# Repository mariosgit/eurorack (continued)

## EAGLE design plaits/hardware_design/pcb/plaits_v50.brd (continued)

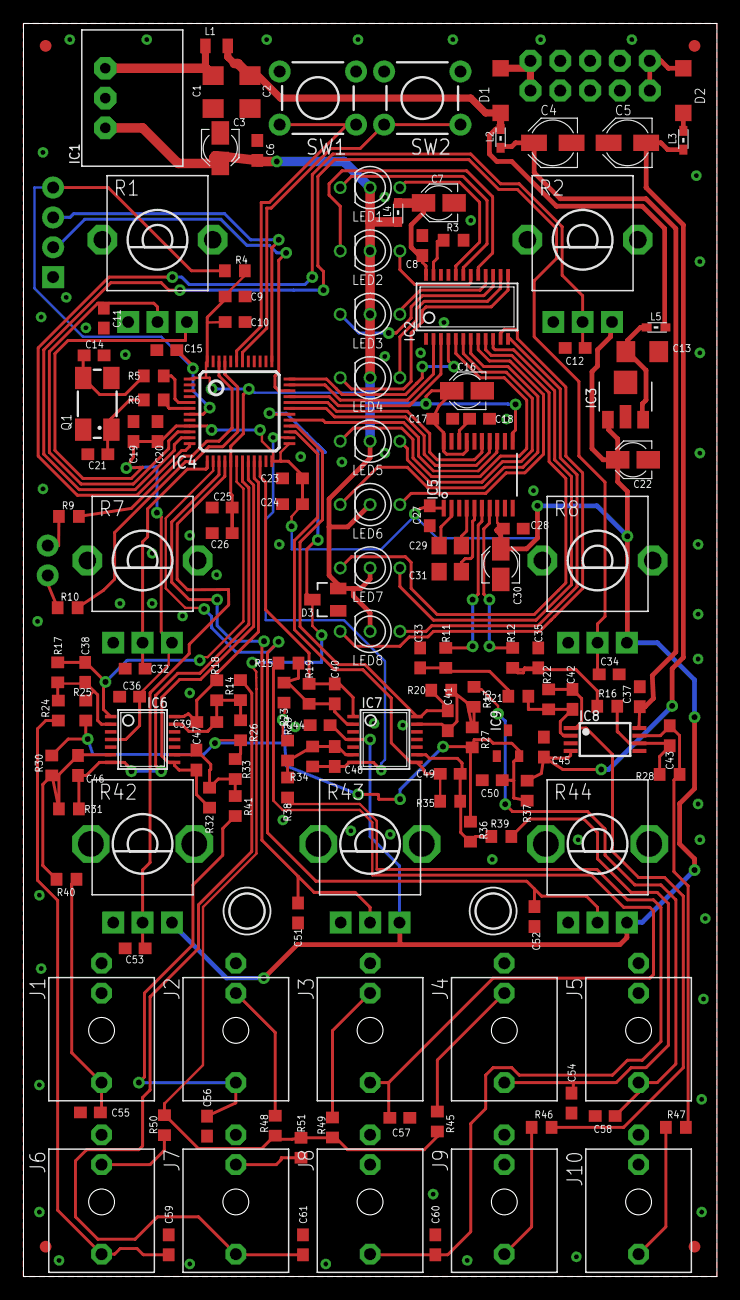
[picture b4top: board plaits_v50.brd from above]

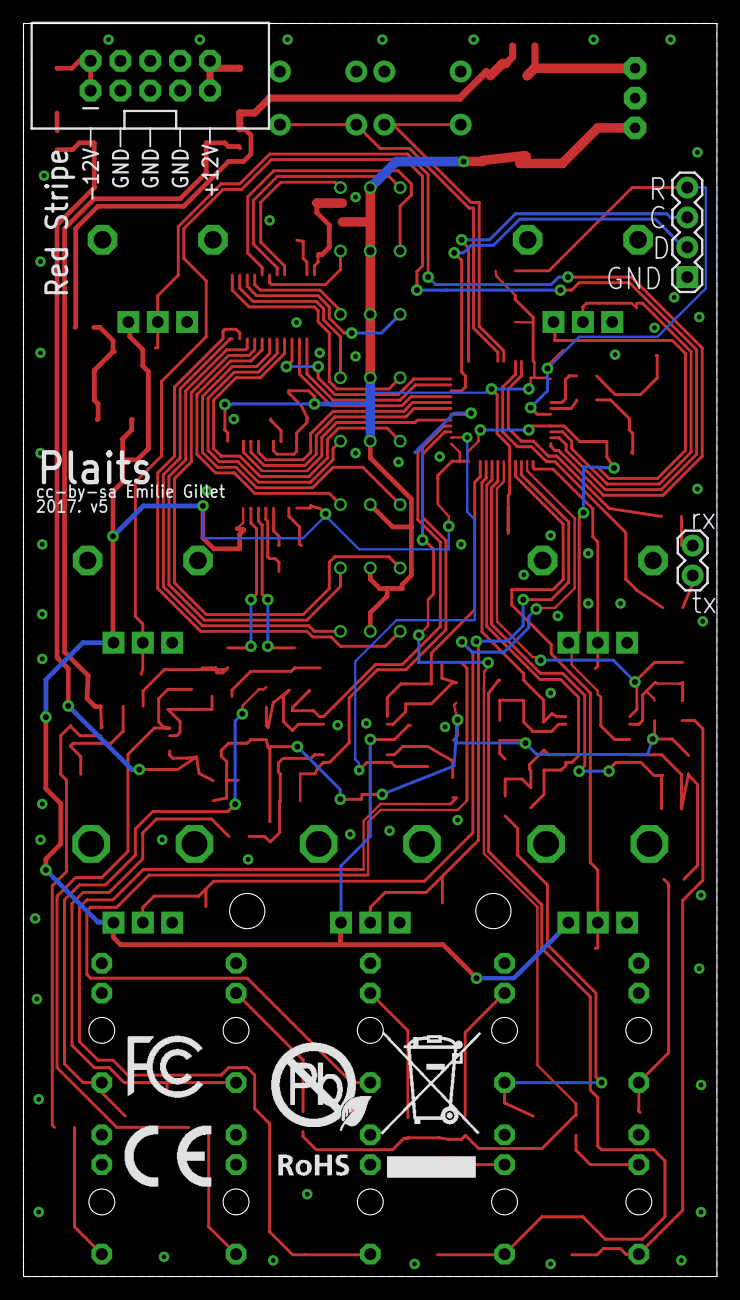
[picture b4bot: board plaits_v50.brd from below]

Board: 2 copper layers, 59.0 x 106.7 mm, 162 parts (6 on the bottom side), 100 nets.

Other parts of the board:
U$1: FCC_MEDIUM
U$2: ROHS_BIG
U$3: CE_MEDIUM

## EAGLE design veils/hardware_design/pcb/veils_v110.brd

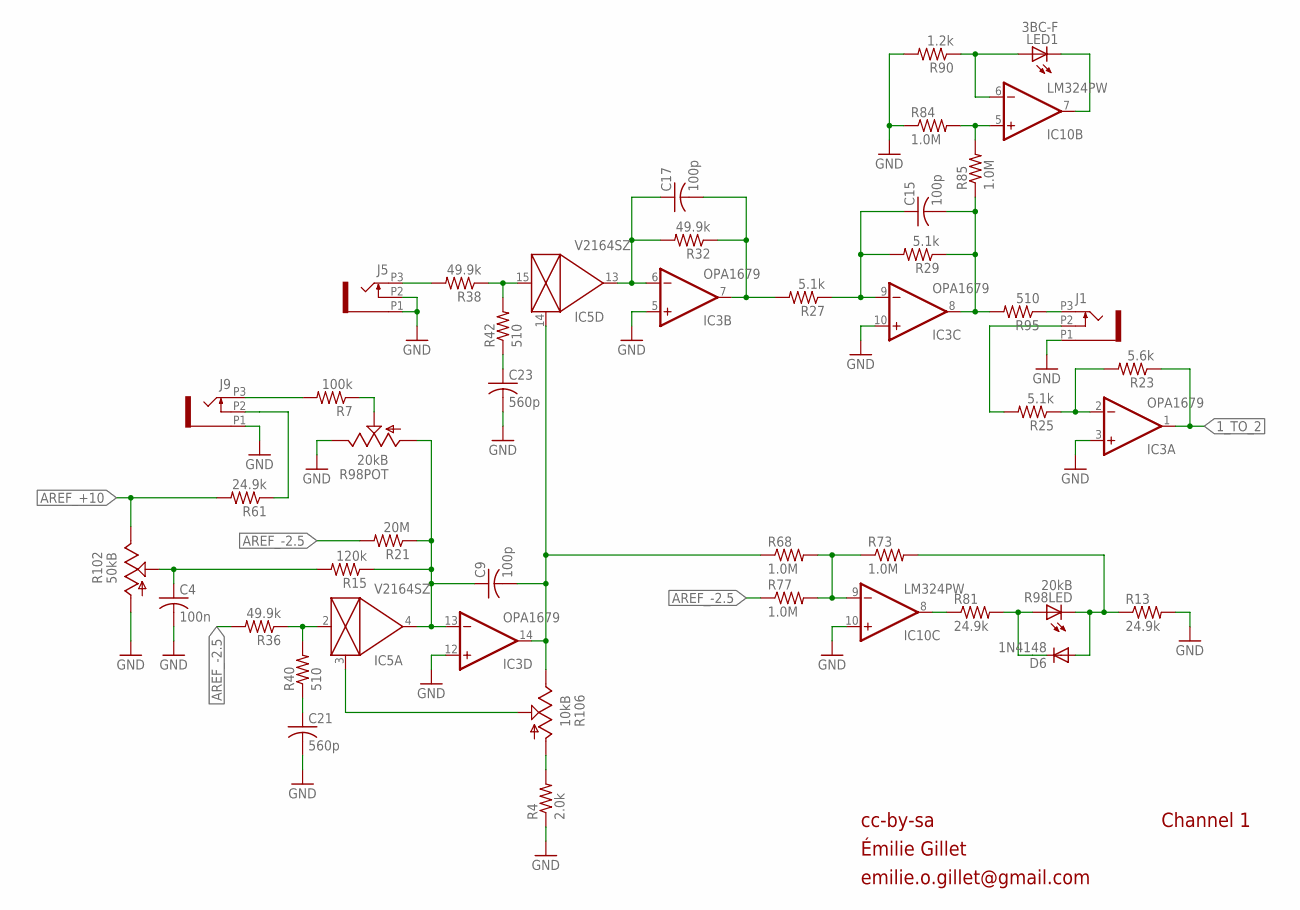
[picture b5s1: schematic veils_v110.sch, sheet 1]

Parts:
C4: 100n; C0402
C9, C15, C17: 100p; C0402
C21, C23: 560p; C0402
D6: 1N4148; SOD523
IC3: OPA1679; TSSOP14_065
IC5: V2164SZ; SOIC16N
IC10: LM324PW; TSSOP14_065
J1, J5, J9: PJ301_THONKICONNTME; WQP_PJ_301M_TME
LED1: 3BC-F; LED3MM
R4: 2.0k; R0402
R7: 100k; R0402
R13, R61, R81: 24.9k; R0402
R15: 120k; R0402
R21: 20M; R0402
R23: 5.6k; R0402
R25, R27, R29: 5.1k; R0402
R32, R36, R38: 49.9k; R0402
R40, R42: 510; R0402
R68, R73, R77, R84, R85: 1.0M; R0402
R90: 1.2k; R0402
R95: 510; R0603
R98: 20kB; BOURNS_SLIDER
R102: 50kB; ALPS_POT_NARROW
R106: 10kB; ALPS_POT_NARROW

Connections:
1_TO_2: IC3.1 (OUT), R23.1; also elsewhere on the board
AREF_+10: R61.2, R102.P$1 (E); also elsewhere on the board
AREF_-2.5: R21.2, R36.2, R77.1; also elsewhere on the board
CV_IN_1: J9.P3 (3), R7.2
FOO: IC5.2 (IN), R36.1, R40.2
GND: C4.2, C21.2, C23.2, IC3.3 (+IN), IC3.5 (+IN), IC3.10 (+IN), IC3.12 (+IN), IC10.10 (+IN), J1.P1 (1), J5.P1 (1), J5.P2 (2), J9.P1 (1), R4.1, R13.2, R84.1, R90.2, R98.3 (E), R102.P$3 (A); also elsewhere on the board
unnamed: IC10.5 (+IN), R84.2, R85.2
unnamed: J1.P3 (3), R95.1
unnamed: IC5.3 (CTRL), R106.P$2 (S)
unnamed: C15.1, IC3.9 (-IN), R27.1, R29.2
unnamed: C4.1, R15.2, R102.P$2 (S)
unnamed: R4.2, R106.P$3 (A)
unnamed: IC10.7 (OUT), LED1.K (C)
unnamed: IC10.6 (-IN), LED1.A, R90.1
unnamed: C21.1, R40.1
unnamed: IC3.2 (-IN), R23.2, R25.1
unnamed: J1.P2 (2), R25.2
unnamed: J9.P2 (2), R61.1
unnamed: R7.1, R98.2 (S)
unnamed: C23.1, R42.1
unnamed: IC10.8 (OUT), R81.1
unnamed: D6.A, R13.1, R73.2, R98.E (C)
unnamed: IC10.9 (-IN), R68.2, R73.1, R77.2
unnamed: C9.1, IC3.13 (-IN), IC5.4 (OUT), R15.1, R21.1, R98.1 (A)
unnamed: J5.P3 (3), R38.2
unnamed: IC5.15 (IN), R38.1, R42.2
unnamed: C9.2, IC3.14 (OUT), IC5.14 (CTRL), R68.1, R106.P$1 (E)
unnamed: C17.1, IC3.6 (-IN), IC5.13 (OUT), R32.2
unnamed: C17.2, IC3.7 (OUT), R27.2, R32.1
OUT1: C15.2, IC3.8 (OUT), R29.1, R85.1, R95.2
PROT1: D6.C, R81.2, R98.B (A)

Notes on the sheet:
cc-by-sa
Channel 1
Émilie Gillet
emilie.o.gillet@gmail.com

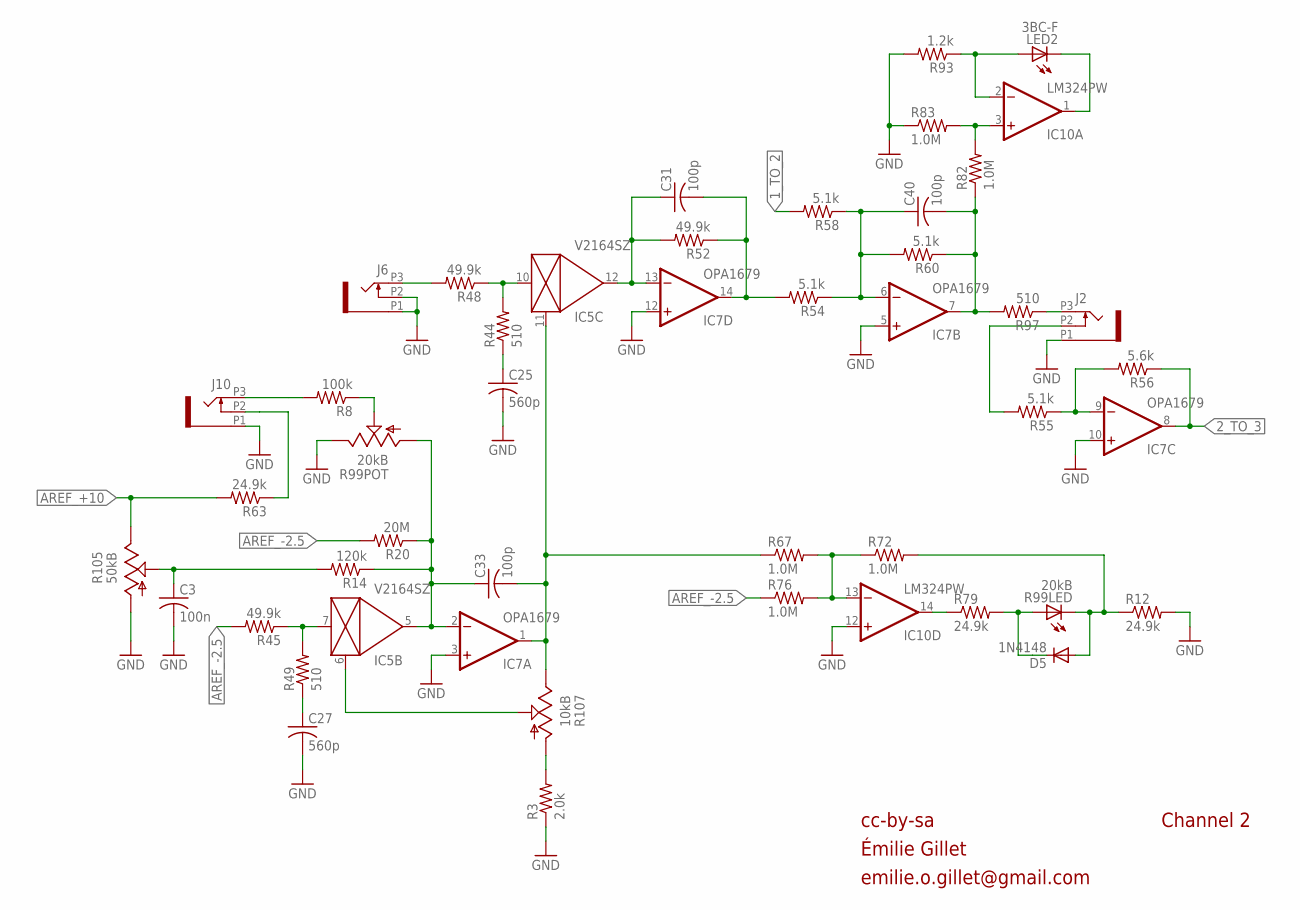
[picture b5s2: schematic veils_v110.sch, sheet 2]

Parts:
C3: 100n; C0402
C25, C27: 560p; C0402
C31, C33, C40: 100p; C0402
D5: 1N4148; SOD523
IC5: V2164SZ; SOIC16N
IC7: OPA1679; TSSOP14_065
IC10: LM324PW; TSSOP14_065
J2, J6, J10: PJ301_THONKICONNTME; WQP_PJ_301M_TME
LED2: 3BC-F; LED3MM
R3: 2.0k; R0402
R8: 100k; R0402
R12, R63, R79: 24.9k; R0402
R14: 120k; R0402
R20: 20M; R0402
R44, R49: 510; R0402
R45, R48, R52: 49.9k; R0402
R54, R55, R58, R60: 5.1k; R0402
R56: 5.6k; R0402
R67, R72, R76, R82, R83: 1.0M; R0402
R93: 1.2k; R0402
R97: 510; R0603
R99: 20kB; BOURNS_SLIDER
R105: 50kB; ALPS_POT_NARROW
R107: 10kB; ALPS_POT_NARROW

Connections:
1_TO_2: R58.2; also elsewhere on the board
2_TO_3: IC7.8 (OUT), R56.1; also elsewhere on the board
AREF_+10: R63.2, R105.P$1 (E); also elsewhere on the board
AREF_-2.5: R20.2, R45.2, R76.1; also elsewhere on the board
FOO1: IC5.7 (IN), R45.1, R49.2
GND: C3.2, C25.2, C27.2, IC7.3 (+IN), IC7.5 (+IN), IC7.10 (+IN), IC7.12 (+IN), IC10.12 (+IN), J2.P1 (1), J6.P1 (1), J6.P2 (2), J10.P1 (1), R3.1, R12.2, R83.1, R93.2, R99.3 (E), R105.P$3 (A); also elsewhere on the board
unnamed: J6.P3 (3), R48.2
unnamed: IC10.3 (+IN), R82.2, R83.2
unnamed: J2.P3 (3), R97.1
unnamed: C25.1, R44.1
unnamed: J10.P2 (2), R63.1
unnamed: IC5.10 (IN), R44.2, R48.1
unnamed: IC5.6 (CTRL), R107.P$2 (S)
unnamed: C40.1, IC7.6 (-IN), R54.1, R58.1, R60.2
unnamed: R3.2, R107.P$3 (A)
unnamed: R8.1, R99.2 (S)
unnamed: IC10.1 (OUT), LED2.K (C)
unnamed: IC10.2 (-IN), LED2.A, R93.1
unnamed: IC7.9 (-IN), R55.1, R56.2
unnamed: J2.P2 (2), R55.2
unnamed: C31.2, IC7.14 (OUT), R52.1, R54.2
unnamed: J10.P3 (3), R8.2
unnamed: C27.1, R49.1
unnamed: C33.1, IC5.5 (OUT), IC7.2 (-IN), R14.1, R20.1, R99.1 (A)
unnamed: C31.1, IC5.12 (OUT), IC7.13 (-IN), R52.2
unnamed: D5.A, R12.1, R72.2, R99.E (C)
unnamed: IC10.14 (OUT), R79.1
unnamed: IC10.13 (-IN), R67.2, R72.1, R76.2
unnamed: C33.2, IC5.11 (CTRL), IC7.1 (OUT), R67.1, R107.P$1 (E)
unnamed: C3.1, R14.2, R105.P$2 (S)
OUT2: C40.2, IC7.7 (OUT), R60.1, R82.1, R97.2
PROT2: D5.C, R79.2, R99.B (A)

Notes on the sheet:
cc-by-sa
Émilie Gillet
emilie.o.gillet@gmail.com
Channel 2

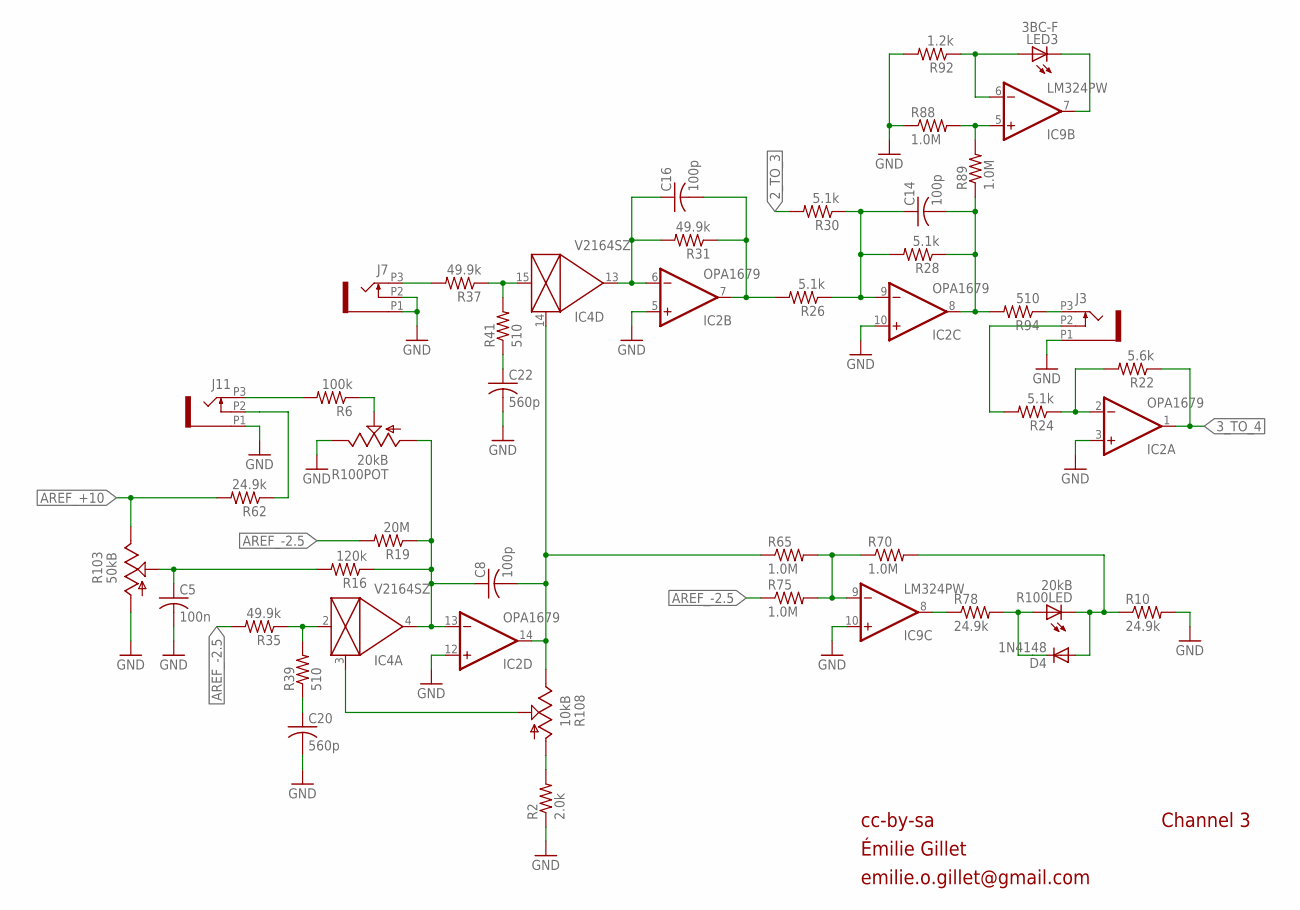
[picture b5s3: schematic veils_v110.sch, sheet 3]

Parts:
C5: 100n; C0402
C8, C14, C16: 100p; C0402
C20, C22: 560p; C0402
D4: 1N4148; SOD523
IC2: OPA1679; TSSOP14_065
IC4: V2164SZ; SOIC16N
IC9: LM324PW; TSSOP14_065
J3, J7, J11: PJ301_THONKICONNTME; WQP_PJ_301M_TME
LED3: 3BC-F; LED3MM
R2: 2.0k; R0402
R6: 100k; R0402
R10, R62, R78: 24.9k; R0402
R16: 120k; R0402
R19: 20M; R0402
R22: 5.6k; R0402
R24, R26, R28, R30: 5.1k; R0402
R31, R35, R37: 49.9k; R0402
R39, R41: 510; R0402
R65, R70, R75, R88, R89: 1.0M; R0402
R92: 1.2k; R0402
R94: 510; R0603
R100: 20kB; BOURNS_SLIDER
R103: 50kB; ALPS_POT_NARROW
R108: 10kB; ALPS_POT_NARROW

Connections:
2_TO_3: R30.2; also elsewhere on the board
3_TO_4: IC2.1 (OUT), R22.1; also elsewhere on the board
AREF_+10: R62.2, R103.P$1 (E); also elsewhere on the board
AREF_-2.5: R19.2, R35.2, R75.1; also elsewhere on the board
FOO2: IC4.2 (IN), R35.1, R39.2
GND: C5.2, C20.2, C22.2, IC2.3 (+IN), IC2.5 (+IN), IC2.10 (+IN), IC2.12 (+IN), IC9.10 (+IN), J3.P1 (1), J7.P1 (1), J7.P2 (2), J11.P1 (1), R2.1, R10.2, R88.1, R92.2, R100.3 (E), R103.P$3 (A); also elsewhere on the board
unnamed: IC9.5 (+IN), R88.2, R89.2
unnamed: J3.P3 (3), R94.1
unnamed: IC4.3 (CTRL), R108.P$2 (S)
unnamed: R2.2, R108.P$3 (A)
unnamed: J11.P3 (3), R6.2
unnamed: C22.1, R41.1
unnamed: IC4.15 (IN), R37.1, R41.2
unnamed: C14.1, IC2.9 (-IN), R26.1, R28.2, R30.1
unnamed: J7.P3 (3), R37.2
unnamed: C16.1, IC2.6 (-IN), IC4.13 (OUT), R31.2
unnamed: IC9.7 (OUT), LED3.K (C)
unnamed: IC9.6 (-IN), LED3.A, R92.1
unnamed: IC2.2 (-IN), R22.2, R24.1
unnamed: J3.P2 (2), R24.2
unnamed: C20.1, R39.1
unnamed: R6.1, R100.2 (S)
unnamed: C8.1, IC2.13 (-IN), IC4.4 (OUT), R16.1, R19.1, R100.1 (A)
unnamed: IC9.8 (OUT), R78.1
unnamed: D4.A, R10.1, R70.2, R100.E (C)
unnamed: IC9.9 (-IN), R65.2, R70.1, R75.2
unnamed: C8.2, IC2.14 (OUT), IC4.14 (CTRL), R65.1, R108.P$1 (E)
unnamed: J11.P2 (2), R62.1
unnamed: C5.1, R16.2, R103.P$2 (S)
unnamed: C16.2, IC2.7 (OUT), R26.2, R31.1
OUT3: C14.2, IC2.8 (OUT), R28.1, R89.1, R94.2
PROT3: D4.C, R78.2, R100.B (A)

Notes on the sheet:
cc-by-sa
Channel 3
Émilie Gillet
emilie.o.gillet@gmail.com

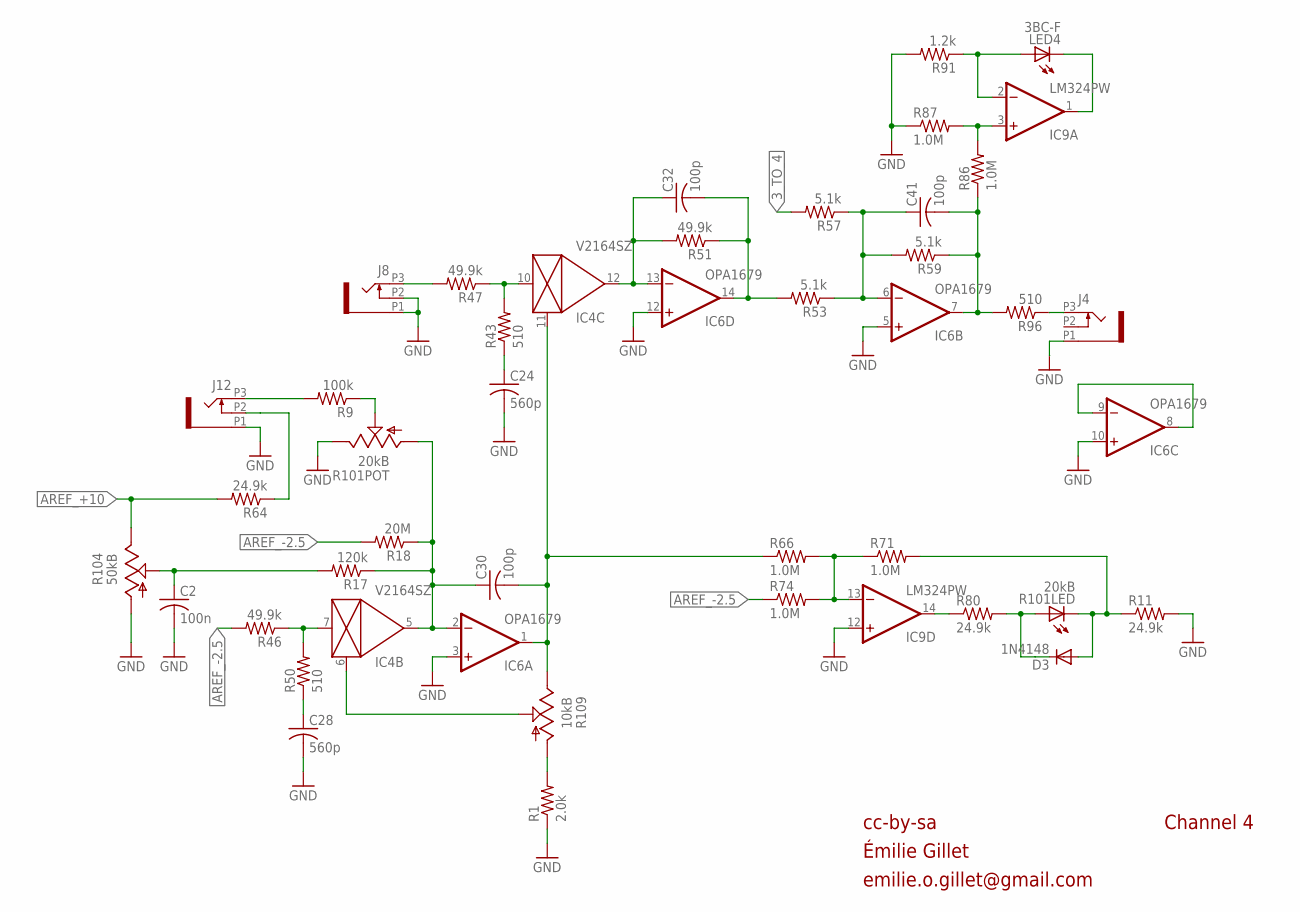
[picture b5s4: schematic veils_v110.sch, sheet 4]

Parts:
C2: 100n; C0402
C24, C28: 560p; C0402
C30, C32, C41: 100p; C0402
D3: 1N4148; SOD523
IC4: V2164SZ; SOIC16N
IC6: OPA1679; TSSOP14_065
IC9: LM324PW; TSSOP14_065
J4, J8, J12: PJ301_THONKICONNTME; WQP_PJ_301M_TME
LED4: 3BC-F; LED3MM
R1: 2.0k; R0402
R9: 100k; R0402
R11, R64, R80: 24.9k; R0402
R17: 120k; R0402
R18: 20M; R0402
R43, R50: 510; R0402
R46, R47, R51: 49.9k; R0402
R53, R57, R59: 5.1k; R0402
R66, R71, R74, R86, R87: 1.0M; R0402
R91: 1.2k; R0402
R96: 510; R0603
R101: 20kB; BOURNS_SLIDER
R104: 50kB; ALPS_POT_NARROW
R109: 10kB; ALPS_POT_NARROW

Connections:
3_TO_4: R57.2; also elsewhere on the board
AREF_+10: R64.2, R104.P$1 (E); also elsewhere on the board
AREF_-2.5: R18.2, R46.2, R74.1; also elsewhere on the board
FOO3: IC4.7 (IN), R46.1, R50.2
GND: C2.2, C24.2, C28.2, IC6.3 (+IN), IC6.5 (+IN), IC6.10 (+IN), IC6.12 (+IN), IC9.12 (+IN), J4.P1 (1), J8.P1 (1), J8.P2 (2), J12.P1 (1), R1.1, R11.2, R87.1, R91.2, R101.3 (E), R104.P$3 (A); also elsewhere on the board
unnamed: IC6.8 (OUT), IC6.9 (-IN)
unnamed: IC9.3 (+IN), R86.2, R87.2
unnamed: IC4.6 (CTRL), R109.P$2 (S)
unnamed: J12.P2 (2), R64.1
unnamed: R1.2, R109.P$3 (A)
unnamed: J12.P3 (3), R9.2
unnamed: C32.1, IC4.12 (OUT), IC6.13 (-IN), R51.2
unnamed: J8.P3 (3), R47.2
unnamed: R9.1, R101.2 (S)
unnamed: J4.P3 (3), R96.1
unnamed: C24.1, R43.1
unnamed: IC4.10 (IN), R43.2, R47.1
unnamed: C41.1, IC6.6 (-IN), R53.1, R57.1, R59.2
unnamed: IC9.1 (OUT), LED4.K (C)
unnamed: IC9.2 (-IN), LED4.A, R91.1
unnamed: IC9.14 (OUT), R80.1
unnamed: C32.2, IC6.14 (OUT), R51.1, R53.2
unnamed: C28.1, R50.1
unnamed: C30.1, IC4.5 (OUT), IC6.2 (-IN), R17.1, R18.1, R101.1 (A)
unnamed: D3.A, R11.1, R71.2, R101.E (C)
unnamed: IC9.13 (-IN), R66.2, R71.1, R74.2
unnamed: C30.2, IC4.11 (CTRL), IC6.1 (OUT), R66.1, R109.P$1 (E)
unnamed: C2.1, R17.2, R104.P$2 (S)
OUT4: C41.2, IC6.7 (OUT), R59.1, R86.1, R96.2
PROT4: D3.C, R80.2, R101.B (A)

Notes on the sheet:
cc-by-sa
Channel 4
Émilie Gillet
emilie.o.gillet@gmail.com

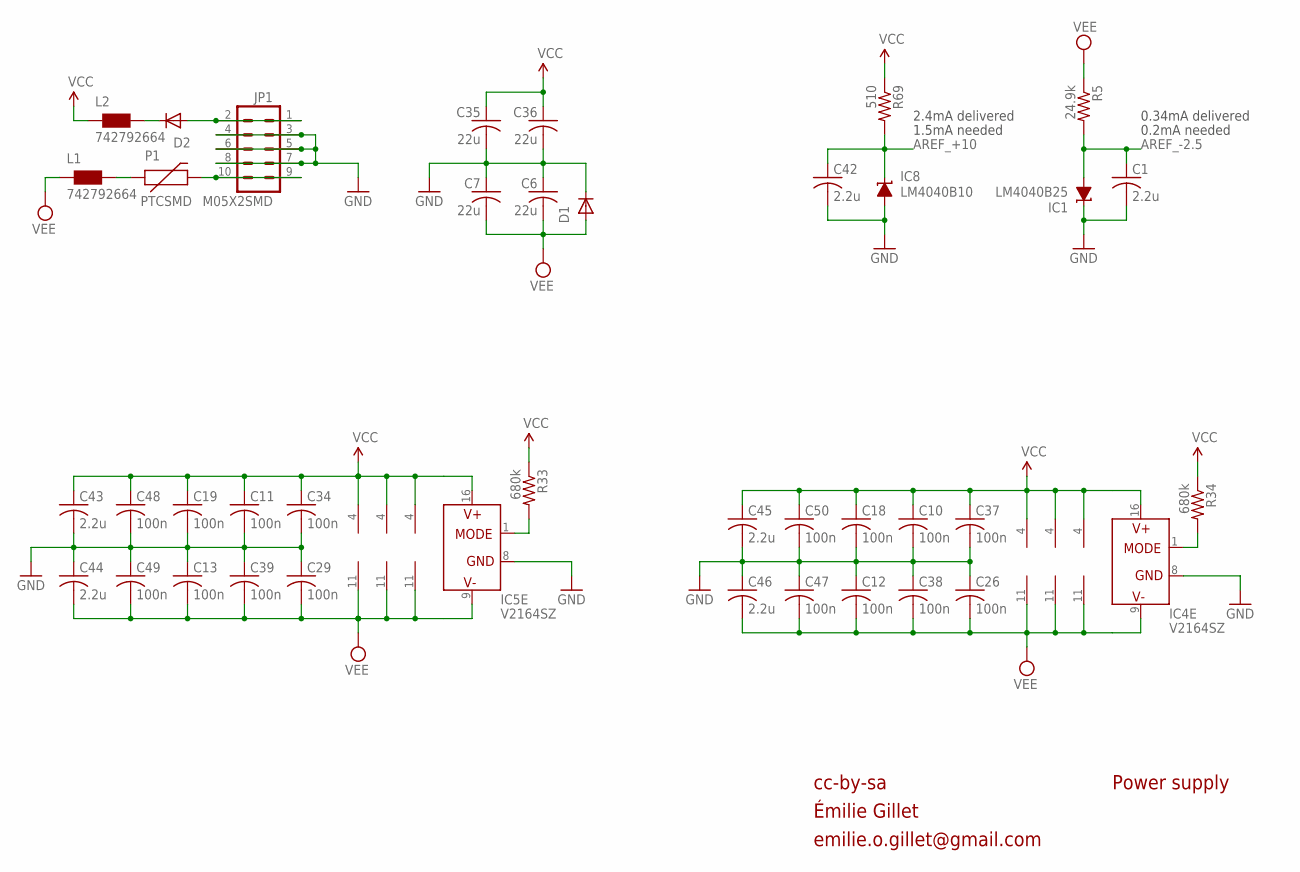
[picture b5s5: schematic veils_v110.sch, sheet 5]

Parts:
C1, C42, C43, C44, C45, C46: 2.2u; C0603
C6, C7, C35, C36: 22u; C1206
C10, C11, C12, C13, C18, C19, C26, C29, C34, C37, C38, C39, C47, C48, C49, C50: 100n; C0402
D1, D2: 1N5819HW; SOD123
IC1: LM4040B25; DBZ_R-PDSO-G3
IC2, IC3, IC6, IC7: OPA1679; TSSOP14_065
IC4, IC5: V2164SZ; SOIC16N
IC8: LM4040B10; DBZ_R-PDSO-G3
IC9, IC10: LM324PW; TSSOP14_065
JP1: M05X2SMD; 2X5-SMD
L1, L2: 742792664; 0603
P1: PTCSMD; PTC-1206
R5: 24.9k; R0402
R33, R34: 680k; R0402
R69: 510; R0402

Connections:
AREF_+10: C42.1, IC8.1 (C), R69.2; also elsewhere on the board
AREF_-2.5: C1.1, IC1.2 (A), R5.2; also elsewhere on the board
GND: C1.2, C6.1, C7.1, C10.2, C11.2, C12.1, C13.1, C18.2, C19.2, C26.1, C29.1, C34.2, C35.2, C36.2, C37.2, C38.1, C39.1, C42.2, C43.2, C44.1, C45.2, C46.1, C47.1, C48.2, C49.1, C50.2, D1.C, IC1.1 (C), IC4.8 (GND), IC5.8 (GND), IC8.2 (A), JP1.3, JP1.4, JP1.5, JP1.6, JP1.7, JP1.8; also elsewhere on the board
unnamed: D2.A, JP1.1, JP1.2
unnamed: JP1.9, JP1.10, P1.2
unnamed: L1.2, P1.1
unnamed: D2.C, L2.2
unnamed: IC5.1 (MODE), R33.2
unnamed: IC4.1 (MODE), R34.2
VCC: C10.1, C11.1, C18.1, C19.1, C34.1, C35.1, C36.1, C37.1, C43.1, C45.1, C48.1, C50.1, IC2.4 (V+), IC3.4 (V+), IC4.16 (V+), IC5.16 (V+), IC6.4 (V+), IC7.4 (V+), IC9.4 (V+), IC10.4 (V+), L2.1, R33.1, R34.1, R69.1
VEE: C6.2, C7.2, C12.2, C13.2, C26.2, C29.2, C38.2, C39.2, C44.2, C46.2, C47.2, C49.2, D1.A, IC2.11 (V-), IC3.11 (V-), IC4.9 (V-), IC5.9 (V-), IC6.11 (V-), IC7.11 (V-), IC9.11 (V-), IC10.11 (V-), L1.1, R5.1

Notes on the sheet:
cc-by-sa
Power supply
0.34mA delivered
2.4mA delivered
0.2mA needed
1.5mA needed
Émilie Gillet
emilie.o.gillet@gmail.com

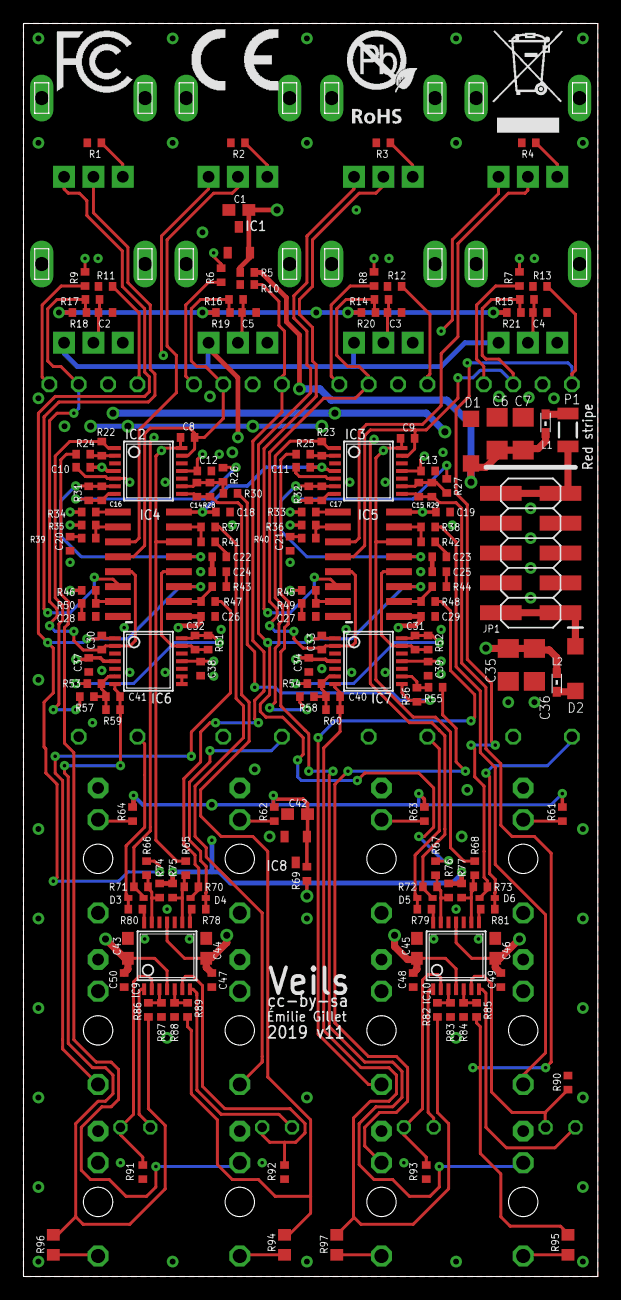
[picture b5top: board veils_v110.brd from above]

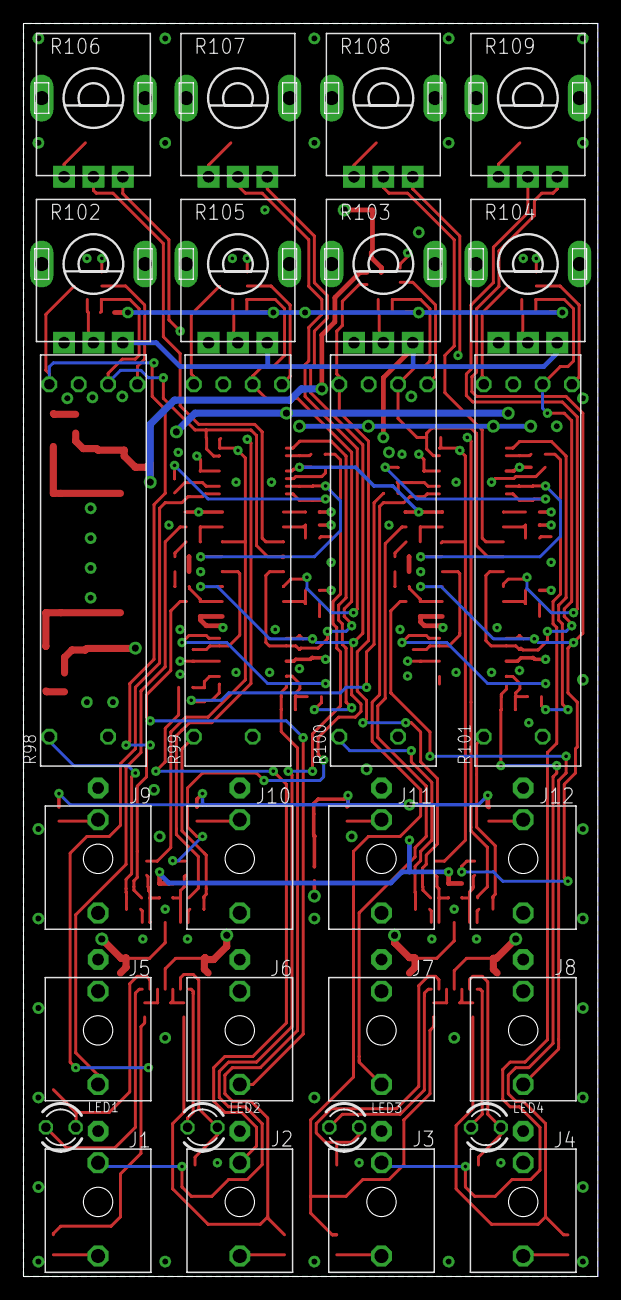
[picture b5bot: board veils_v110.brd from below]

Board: 4 copper layers, 48.9 x 106.7 mm, 199 parts (28 on the bottom side), 121 nets.

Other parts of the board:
U$1: CE_MEDIUM
U$2: FCC_MEDIUM
U$3: ROHS_LOGO
U$4: TRASHCAN_LOGO

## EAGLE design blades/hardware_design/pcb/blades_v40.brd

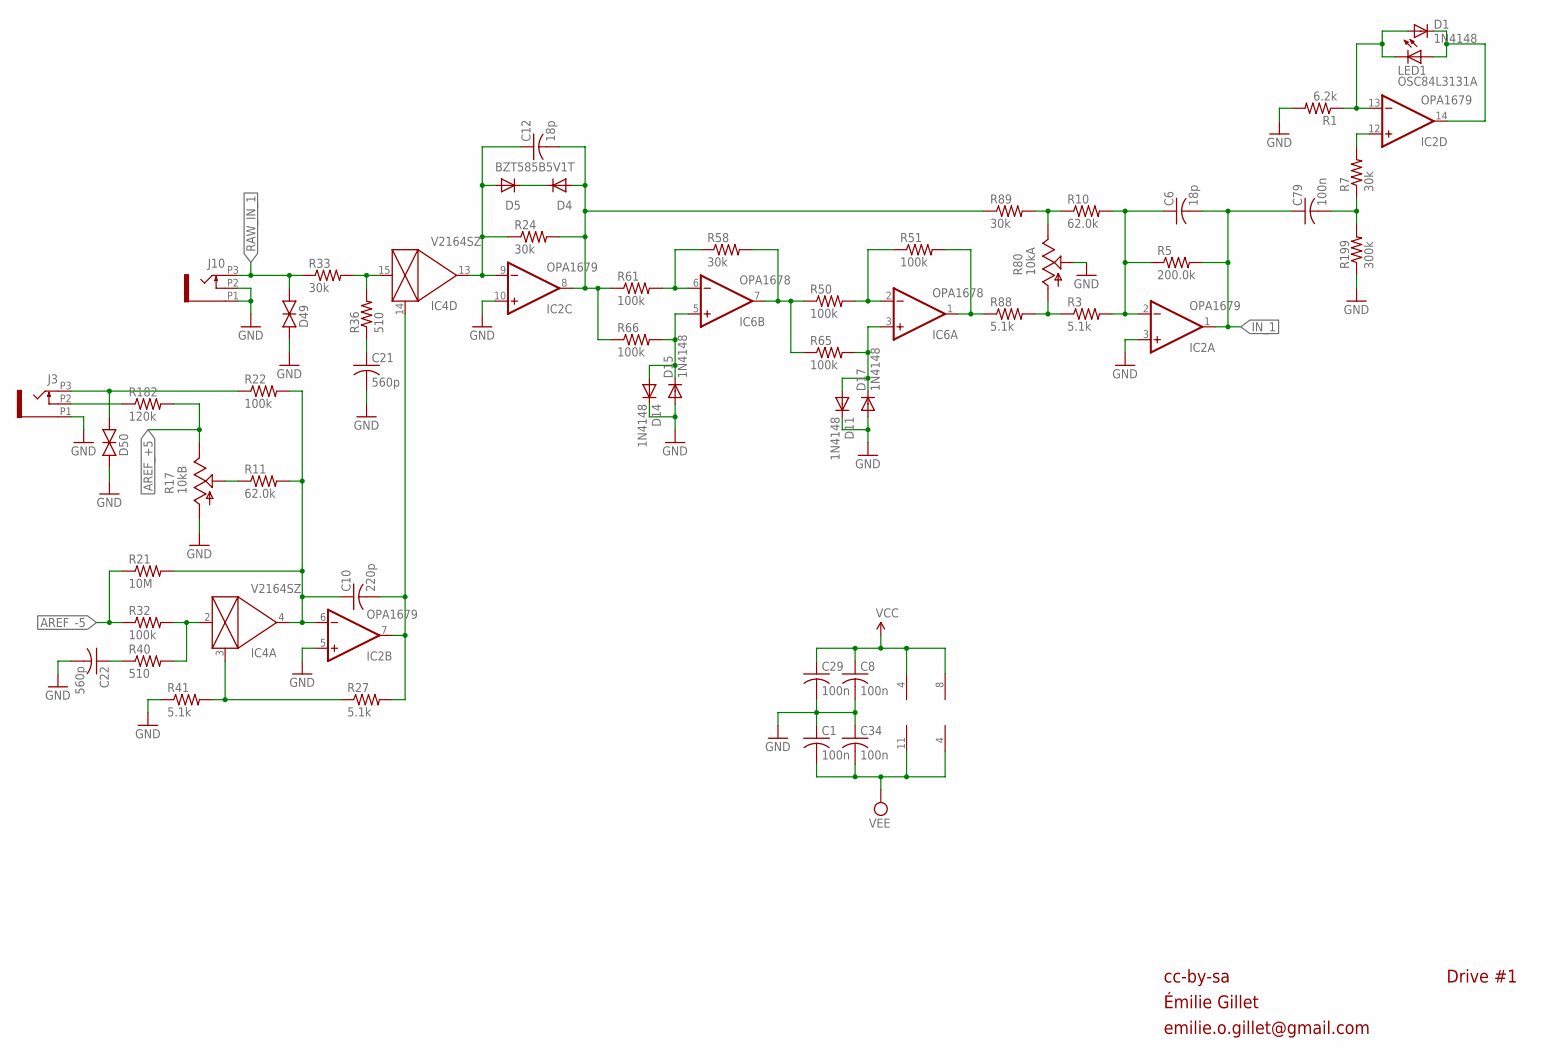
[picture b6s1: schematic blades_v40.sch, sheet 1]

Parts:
C1, C8, C29, C34, C79: 100n; C0402
C6, C12: 18p; C0402
C10: 220p; C0402
C21, C22: 560p; C0402
D1, D11, D14, D15, D17: 1N4148; SOD523
D4, D5: BZT585B5V1T; SOD523
D49, D50: TVS; 0603
IC2: OPA1679; TSSOP14_065
IC4: V2164SZ; SOIC16N
IC6: OPA1678; VSSOP8
J3, J10: PJ301_THONKICONNTME; WQP_PJ_301M_TME
LED1: OSC84L3131A; LED3MM
R1: 6.2k; R0402
R3, R27, R41, R88: 5.1k; R0402
R5: 200.0k; R0402
R7, R24, R33, R58, R89: 30k; R0402
R10, R11: 62.0k; R0402
R17: 10kB; ALPS_POT_VERTICAL_PS
R21: 10M; R0402
R22, R32, R50, R51, R61, R65, R66: 100k; R0402
R36, R40: 510; R0402
R80: 10kA; ALPS_POT_NARROW
R182: 120k; R0402
R199: 300k; R0402

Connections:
AREF_+5: R17.P$1 (E), R182.2; also elsewhere on the board
AREF_-5: R21.1, R32.1; also elsewhere on the board
DRIVE_1: C12.2, D4.A, IC2.8 (OUT), R24.2, R61.1, R66.1, R89.1
GND: C1.1, C8.2, C21.2, C22.2, C29.2, C34.1, D11.C, D14.C, D15.A, D17.A, D49.1 (A), D50.1 (A), IC2.3 (+IN), IC2.5 (+IN), IC2.10 (+IN), J3.P1 (1), J10.P1 (1), J10.P2 (2), R1.2, R17.P$3 (A), R41.1, R80.P$2 (S), R199.1; also elsewhere on the board
IN_1: C6.2, C79.1, IC2.1 (OUT), R5.2; also elsewhere on the board
MORPH_1A1: C10.2, IC2.7 (OUT), IC4.14 (CTRL), R27.2
unnamed: D4.C, D5.C
unnamed: C21.1, R36.1
unnamed: C79.2, R7.1, R199.2
unnamed: IC4.2 (IN), R32.2, R40.2
unnamed: IC2.12 (+IN), R7.2
unnamed: R10.1, R80.P$1 (E), R89.2
unnamed: IC6.6 (-IN), R58.1, R61.2
unnamed: D50.2 (C), J3.P3 (3), R22.1
unnamed: C10.1, IC2.6 (-IN), IC4.4 (OUT), R11.2, R21.2, R22.2
unnamed: R3.1, R80.P$3 (A), R88.2
unnamed: C6.1, IC2.2 (-IN), R3.2, R5.1, R10.2
unnamed: R11.1, R17.P$2 (S)
unnamed: IC4.3 (CTRL), R27.1, R41.2
unnamed: J3.P2 (2), R182.1
unnamed: C22.1, R40.1
unnamed: IC4.15 (IN), R33.2, R36.2
unnamed: D1.A, IC2.13 (-IN), LED1.K (C), R1.1
unnamed: C12.1, D5.A, IC2.9 (-IN), IC4.13 (OUT), R24.1
unnamed: D14.A, D15.C, IC6.5 (+IN), R66.2
unnamed: D1.C, IC2.14 (OUT), LED1.A
unnamed: IC6.7 (OUT), R50.1, R58.2, R65.1
unnamed: IC6.2 (-IN), R50.2, R51.1
unnamed: IC6.1 (OUT), R51.2, R88.1
unnamed: D11.A, D17.C, IC6.3 (+IN), R65.2
RAW_IN_1: D49.2 (C), J10.P3 (3), R33.1; also elsewhere on the board
VCC: C8.1, C29.1, IC2.4 (V+), IC6.8 (V+); also elsewhere on the board
VEE: C1.2, C34.2, IC2.11 (V-), IC6.4 (V-); also elsewhere on the board

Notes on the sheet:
cc-by-sa
Émilie Gillet
emilie.o.gillet@gmail.com
Drive #1

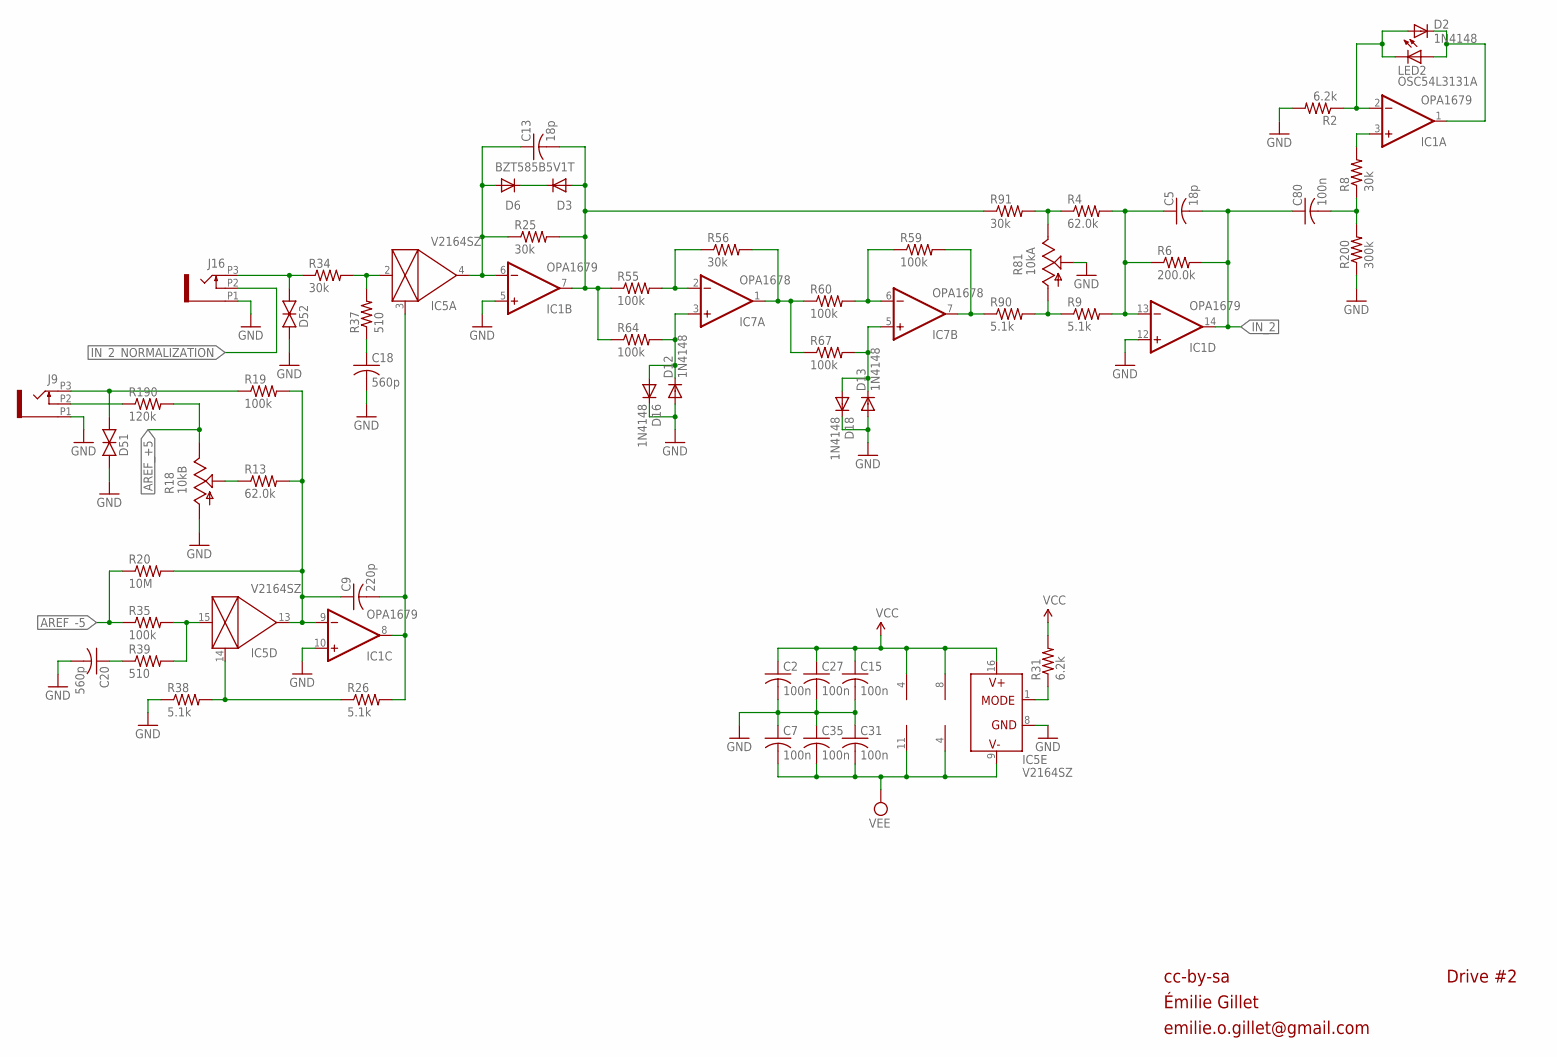
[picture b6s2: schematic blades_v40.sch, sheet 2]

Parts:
C2, C7, C15, C27, C31, C35, C80: 100n; C0402
C5, C13: 18p; C0402
C9: 220p; C0402
C18, C20: 560p; C0402
D2, D12, D13, D16, D18: 1N4148; SOD523
D3, D6: BZT585B5V1T; SOD523
D51, D52: TVS; 0603
IC1: OPA1679; TSSOP14_065
IC5: V2164SZ; SOIC16N
IC7: OPA1678; VSSOP8
J9, J16: PJ301_THONKICONNTME; WQP_PJ_301M_TME
LED2: OSC54L3131A; LED3MM
R2, R31: 6.2k; R0402
R4, R13: 62.0k; R0402
R6: 200.0k; R0402
R8, R25, R34, R56, R91: 30k; R0402
R9, R26, R38, R90: 5.1k; R0402
R18: 10kB; ALPS_POT_VERTICAL_PS
R19, R35, R55, R59, R60, R64, R67: 100k; R0402
R20: 10M; R0402
R37, R39: 510; R0402
R81: 10kA; ALPS_POT_NARROW
R190: 120k; R0402
R200: 300k; R0402

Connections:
AREF_+5: R18.P$1 (E), R190.2; also elsewhere on the board
AREF_-5: R20.1, R35.1; also elsewhere on the board
DRIVE_2: C13.2, D3.A, IC1.7 (OUT), R25.2, R55.1, R64.1, R91.1
GND: C2.2, C7.1, C15.2, C18.2, C20.2, C27.2, C31.1, C35.1, D12.A, D13.A, D16.C, D18.C, D51.1 (A), D52.1 (A), IC1.5 (+IN), IC1.10 (+IN), IC1.12 (+IN), IC5.8 (GND), J9.P1 (1), J16.P1 (1), R2.2, R18.P$3 (A), R38.1, R81.P$2 (S), R200.1; also elsewhere on the board
IN_1LED1: IC1.3 (+IN), R8.2
IN_2: C5.2, C80.1, IC1.14 (OUT), R6.2; also elsewhere on the board
IN_2_NORMALIZATION: J16.P2 (2); also elsewhere on the board
MORPH_1A2: C9.2, IC1.8 (OUT), IC5.3 (CTRL), R26.2
unnamed: D2.A, IC1.2 (-IN), LED2.K (C), R2.1
unnamed: R13.1, R18.P$2 (S)
unnamed: IC7.2 (-IN), R55.2, R56.1
unnamed: D12.C, D16.A, IC7.3 (+IN), R64.2
unnamed: IC7.1 (OUT), R56.2, R60.1, R67.1
unnamed: IC7.6 (-IN), R59.1, R60.2
unnamed: J9.P2 (2), R190.1
unnamed: IC7.7 (OUT), R59.2, R90.1
unnamed: D51.2 (C), J9.P3 (3), R19.1
unnamed: C5.1, IC1.13 (-IN), R4.2, R6.1, R9.2
unnamed: IC5.1 (MODE), R31.1
unnamed: C80.2, R8.1, R200.2
unnamed: D2.C, IC1.1 (OUT), LED2.A
unnamed: C9.1, IC1.9 (-IN), IC5.13 (OUT), R13.2, R19.2, R20.2
unnamed: IC5.14 (CTRL), R26.1, R38.2
unnamed: IC5.15 (IN), R35.2, R39.2
unnamed: C20.1, R39.1
unnamed: C18.1, R37.1
unnamed: IC5.2 (IN), R34.2, R37.2
unnamed: C13.1, D6.A, IC1.6 (-IN), IC5.4 (OUT), R25.1
unnamed: D13.C, D18.A, IC7.5 (+IN), R67.2
unnamed: R4.1, R81.P$1 (E), R91.2
unnamed: R9.1, R81.P$3 (A), R90.2
unnamed: D3.C, D6.C
RAW_IN_2: D52.2 (C), J16.P3 (3), R34.1
VCC: C2.1, C15.1, C27.1, IC1.4 (V+), IC5.16 (V+), IC7.8 (V+), R31.2; also elsewhere on the board
VEE: C7.2, C31.2, C35.2, IC1.11 (V-), IC5.9 (V-), IC7.4 (V-); also elsewhere on the board

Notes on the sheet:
Drive #2
cc-by-sa
Émilie Gillet
emilie.o.gillet@gmail.com
